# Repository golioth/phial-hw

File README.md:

# Phial

A small (~22 mm diameter, round) battery-powered Bluetooth LE sensor board from
Golioth. Rev B.

> **Status:** pre-release cleanup for open-hardware (OSHW) publication.
> Items marked **[UNKNOWN]** below need confirmation before this README is
> final. Everything else was verified against the design files in this repo.

## Hardware summary (Rev B)

| Subsystem | Part / details | Notes |
|-----------|----------------|-------|
| Main SoC  | Nordic nRF54L15-QFAA | Rev B moved from nRF52 BGA to nRF54L15 DFN |
| PMIC      | Nordic nPM2100 (NPM2100-CAAA-R) | coin-cell optimized |
| IMU       | ST LIS2DH12 | 3-axis accelerometer, I2C |
| Microphone| ST MP34DT05TR-A | PDM MEMS mic |
| Audio out | Raltron RDTE-4.000-3030-NS1 | electromagnetic transducer (buzzer) |
| BLE antenna | Taoglas WLA.04 | 2.4 GHz chip antenna |
| NFC       | Taoglas FXC.24.A flex antenna | nets NFC1/NFC2 |
| Display/UI| 16x 0201 LED ring (Kingbright APG0201SEC-TT) | |
| Buttons   | Panasonic EVP-AWED4A + C&K KMS221G | [UNKNOWN] confirm both populated on Rev B |
| Battery   | CR2032 coin cell (HF1N holder) | [UNKNOWN] role of 112TR contact / alternate battery options |
| Debug     | SWD via Tag-Connect | alignment pins on paste layer |

**[UNKNOWN]** The schematic also references an nRF52840-CKAA-F-R (WLCSP) symbol
and a BME280. It is unclear whether these are an alternate/deprecated variant,
DNP on Rev B, or planned future population. Needs a pass against the Rev B BOM.

## Design files

- KiCad 9 project. **Note:** project files are currently named
  `pilulith.*` (the project's former codename). They are being renamed to
  `phial.*` as part of the release cleanup — see the cleanup checklist.
- 6-layer board, 0.8464 mm thick, ENIG finish, JLC06081H (2116/7628) stackup.
- `input/` — local symbol/footprint/3D sources and reference art.
- `pilulith.pretty/` (to be renamed) — project footprints, including Golioth
  and Orleon logo art footprints.

## Manufacturing outputs

**[UNKNOWN / TODO]** Gerbers, drill files, pick-and-place and BOM exports are
not yet committed or attached to a release. The BOM currently lives in
schematic symbol properties (last touched in commit `e64fb58`). A fabrication
package will be attached to a GitHub Release before publication.

## Firmware

Firmware lives in a separate repo: [golioth/phial-fw](https://github.com/golioth/phial-fw)
(currently private).

## License

Hardware in this repository is released under the **CERN Open Hardware
Licence v2 — Permissive (CERN-OHL-P)**. The LICENSE file is being added as
part of the release cleanup. Documentation and artwork are covered by the
same license unless noted otherwise.

Note: `input/art/` contains vendor reference images (Nordic, JLCPCB stackups,
Taoglas antenna drawings) that are **not** covered by this license and may be
replaced with links before publication — see the cleanup checklist.

## Credits

Designed by Chris Gammell at Golioth.

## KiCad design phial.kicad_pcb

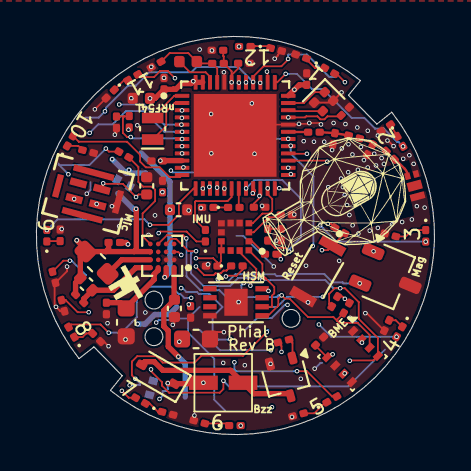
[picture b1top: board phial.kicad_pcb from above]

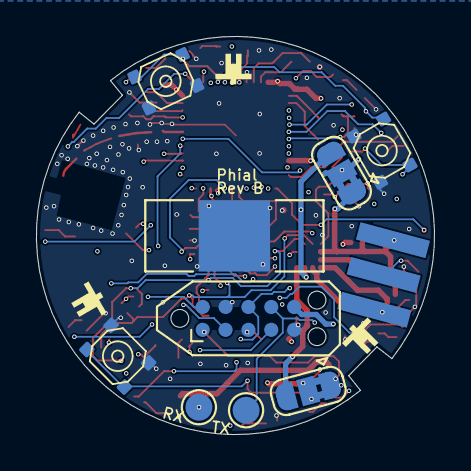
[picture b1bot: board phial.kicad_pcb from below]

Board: 6 copper layers, 22.1 x 22.1 mm, 95 parts (10 on the bottom side), 75 nets.

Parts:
BT101: 112TR; BAT_112TR
C1, C2: 560P; C_0201_0603Metric
C3, C7: 2U2; C_0201_0603Metric
C4: 10N; C_0201_0603Metric
C5: 2N2; C_0201_0603Metric
C6, C9, C101, C105, C107, C118: 0.1U; C_0201_0603Metric
C8, C117: 1P2; C_0201_0603Metric
C10: 22U; C_0603_1608Metric
C11, C16: 1N; C_0201_0603Metric
C12, C108: 10U; C_0402_1005Metric
C13, C14: 2U2; C_0402_1005Metric
C29: 4U7; C_0603_1608Metric
C104: 1U; C_0402_1005Metric
D3: 1N4148W; D_SOD-323
D101, D102, D103, D104, D105, D106, D107, D108, D109, D110, D111, D112: RED; LED_0201_0603Metric
J101: Conn_01x03_Pin; Cabling
J103: Conn_ARM_JTAG_SWD_10; Tag-Connect_TC2050-IDC-NL_2x05_P1.27mm_Vertical
JP1: npm2100-bridge; SolderJumper-3_P1.3mm_Bridged2Bar12_RoundedPad1.0x1.5mm
JP2: sensor-bridge; SolderJumper-3_P1.3mm_Bridged2Bar12_RoundedPad1.0x1.5mm
L1: FB; L_0201_0603Metric
L2: 2u2; L_0603_1608Metric_Pad1.05x0.95mm_HandSolder
L3: 4U7; L_0402_1005Metric
L4: 2N0; L_0201_0603Metric
L101: 3N9; L_0201_0603Metric
L102: 4N7; L_0201_0603Metric
LED13, LED14, LED15, LED16: RED; LED_0201_0603Metric
LS1: RDTE-4.000-3030-NS1
Q1: SBC847; SOT-323_SC-70
R1, R2, R3, R5, R101, R102, R103, R104, R105, R106, R107, R108, R109, R110, R111, R112: R_Small; R_0201_0603Metric
R4, R6, R8, R66: 0; R_0201_0603Metric
R7: 1K; R_0201_0603Metric
R113, R114, R115: 100K; R_0201_0603Metric
R117, R118: 4K7; R_0201_0603Metric
SW1, SW2, SW3: KMT221NG
SW4: KMT221NG; SW_EVP-AWED4A
TP14, TP15: TestPoint; TestPoint_Pad_D1.5mm
U1: NRF54L15-QFAA-R; QFN40P600X600X90-49N
U2: NPM2100-CAAA-R; BGA16N44P4X4_189X191X52N
U10: LIS2DH; SENSOR_LIS2DH12
U102: WLA.04; SMD4_ANT_WLAp04_TAL
U103: ATECC608B-MAHDA; DFN-8-1EP_3x2mm_P0.5mm_EP1.3x1.5mm
U104: LF21115TMR; TSOT-23
U105: BME280; Bosch_LGA-8_2.5x2.5mm_P0.65mm_ClockwisePinNumbering
U106: MP34DT05TR-A; MP34DT05TR-A_STM
Y101: 32MHz; Crystal_SMD_1210-4Pin_1.2x1.0mm
Y102: 32.768K; Crystal_SMD_MicroCrystal_CM9V-T1A-2Pin_1.6x1.0mm

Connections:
/2.07/T0: LED16.2 (A), U1.18 (P2.07/TRACEDATA(0)/SWO)
/2.08/T1: LED13.2 (A), U1.19 (P2.08/TRACEDATA(1))
/2.09/T2: LED14.2 (A), U1.20 (P2.09/TRACEDATA(2))
/2.10/T3: LED15.2 (A), U1.21 (P2.10/TRACEDATA(3))
/ANT_FEED: L4.2, U102.1 (RF_FEED)
/ANT_NRF: L101.1, U1.31 (ANT)
/ANT_PI: C117.2, L101.2, L102.1
/BATTERY_MEAS: R113.1, R114.2, U1.7 (P1.06/ASO(1)/AIN2)
/BOOT: R8.1, SW1.1, SW2.1, SW3.1, U1.40 (P1.12/ASI(3)/RADIO(3)/AIN5)
/BUZZER: R7.1, U1.29 (P0.04/GRTCLFCLKOUT)
/CR2032_V+: C11.1, C12.1, J101.3, JP1.1 (A), L2.1, R6.1, U2.C4 (VBAT)
/IMU_INT: U1.39 (P1.11/ASO(3)/RADIO(2)/AIN4), U10.12 (INT1)
/LED01: D101.2 (A), U1.38 (P1.10/ASI(2)/RADIO(1))
/LED02: D102.2 (A), U1.37 (P1.09/ASO(2)/RADIO(0))
/LED03: D103.2 (A), U1.28 (P0.03/GRTCPWM)
/LED04: D104.2 (A), U1.27 (P0.02)
/LED05: D105.2 (A), U1.17 (P2.06/TRACECLK)
/LED06: D106.2 (A), U1.16 (P2.05)
/LED07: D107.2 (A), U1.15 (P2.04)
/LED08: D108.2 (A), U1.14 (P2.03)
/LED09: D109.2 (A), U1.13 (P2.02)
/LED10: D110.2 (A), U1.12 (P2.01)
/LED11: D111.2 (A), U1.11 (P2.00)
/LED12: D112.2 (A), U1.42 (P1.14/RADIO(5)/AIN7)
/MAG: U1.41 (P1.13/RADIO(4)/AIN6), U104.2 (OUT)
/MIC_CLK: U1.6 (P1.05/ASI(0)/RADIO(6)/AIN1), U106.3 (CLK)
/MIC_DATA: U1.5 (P1.04/ASO(0)/AIN0), U106.4 (DOUT)
/NFC1: C1.1, J101.1, U1.3 (P1.02/NFC1)
/NFC2: C2.2, J101.2, U1.4 (P1.03/NFC2)
/Power_Insert: J103.6 (SWO/TDO), R6.2
/RESET_N: R66.1, SW4.1, U1.30 (~RESET), U2.C1 (PG/RESET)
/SCL: R117.2, U1.24 (P0.01), U2.D2 (SCL), U10.1 (SCL/SPC), U103.6 (SCL), U105.4 (SCK)
/SDA: R118.2, U1.23 (P0.00), U2.D3 (SDA), U10.4 (SDA/SDI/SDO), U103.5 (SDA), U105.3 (SDI)
/SW: L2.2, U2.B4 (SW)
/SWCLK: J103.4 (SWCLK/TCK), U1.26 (SWDCLK)
/SWDIO: J103.2 (SWDIO/TMS), U1.25 (SWDIO)
/VINT-NPM2100: C10.1, C16.1, U2.A3 (VINT)
/VOUT-NPM2100: C14.1, JP1.3 (B), U2.A2 (VOUT)
/VOUTLDO-NPM2100: C13.1, JP2.3 (B), U2.A1 (LSOUT/VOUTLDO)
/nRF52_RX: J103.8 (NC/TDI/RX), TP15.1, U1.8 (P1.07/ASI(1)/AIN3)
/nRF52_TX: J103.7 (TX), TP14.1, U1.9 (P1.08/CLK16M/EXTREF)
DCC: L3.2, U1.46 (DCC)
DECA: C3.1, C4.1, C5.1, L1.1, U1.33 (DECRF), U1.43 (DECA)
DECD: C7.1, L1.2, L3.1, U1.45 (DECD)
GND: BT101.N, C1.2, C2.1, C3.2, C4.2, C5.2, C6.2, C7.2, C8.1, C9.2, C10.2, C13.2, C14.2, C16.2, C29.2, C101.2, C104.2, C105.2, C107.2, C108.2, C117.1, C118.2, J103.3 (GND), J103.5 (GND), J103.9 (GNDDetect), Q1.2 (E), R1.2, R2.2, R3.2, R4.1, R5.2, R101.2, R102.2, R103.2, R104.2, R105.2, R106.2, R107.2, R108.2, R109.2, R110.2, R111.2, R112.2, R114.1, SW1.2, SW2.2, SW3.2, SW4.2, U1.32 (VSS_PA), U1.44 (VSS), U1.49 (VSS), U2.B1 (AVSS1), U2.B2 (AVSS2), U10.5 (RES_5), U10.6 (GND), U10.7 (GND), U10.8 (GND), U102.3 (GND), U102.4 (GND), U103.4 (GND), U103.9 (EP), U104.3 (GND), U105.1 (GND), U105.5 (SDO), U105.7 (GND), U106.5 (GND), Y101.2, Y101.4
unnamed: C8.2, L4.1, L102.2
unnamed: D3.2 (A), LS1.2, Q1.3 (C)
unnamed: D101.1 (K), R101.1
unnamed: D102.1 (K), R102.1
unnamed: D103.1 (K), R103.1
unnamed: D104.1 (K), R104.1
unnamed: D105.1 (K), R105.1
unnamed: D106.1 (K), R106.1
unnamed: D107.1 (K), R107.1
unnamed: D108.1 (K), R108.1
unnamed: D109.1 (K), R109.1
unnamed: D110.1 (K), R110.1
unnamed: D111.1 (K), R111.1
unnamed: D112.1 (K), R112.1
unnamed: J103.10 (~RESET), R66.2
unnamed: LED13.1 (K), R1.1
unnamed: LED14.1 (K), R5.1
unnamed: LED15.1 (K), R2.1
unnamed: LED16.1 (K), R3.1
unnamed: Q1.1 (B), R7.2
unnamed: U1.1 (P1.00/XL1), Y102.2
unnamed: U1.2 (P1.01/XL2), Y102.1
unnamed: U1.34 (XC1), Y101.3
unnamed: U1.35 (XC2), Y101.1
unnamed: C11.2, C12.2, U2.A4 (PVSS)
unnamed: R8.2, U2.D4 (SHPHLD)
unnamed: R115.1, U10.2 (CS)
unnamed: R4.2, U10.3 (SDO/SA0)
VCC: C6.1, C9.1, C101.1, C107.1, C108.1, J103.1 (VTref), JP1.2 (C), JP2.1 (A), R113.2, U1.10 (VDD), U1.22 (VDD), U1.36 (VDD), U1.47 (VDD), U1.48 (VDD)
VSENSOR: C29.1, C104.1, C105.1, C118.1, D3.1 (K), JP2.2 (C), LS1.1, R115.2, R117.1, R118.1, U10.9 (VDD), U10.10 (VDD_IO), U103.8 (VCC), U104.1 (VCC), U105.2 (CSB), U105.6 (VDDIO), U105.8 (VDD), U106.1 (VDD)

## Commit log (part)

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2025-03-07 DRC passes
2025-03-07 Removing additional warnings
2025-03-07 added logo and changed for cheaper process. Found out it's a 22 mm board, whoops
2025-03-07 Rotated battery connector to match the spirulo board cabling
2026-01-15 Modified to use nRF54L15 and DFN instead of BGA nRF52. Moving parts to match
2026-01-16 initial routing complete
2026-01-16 reenable stackup graphic
2026-01-19 putting in a no popped npm2100 for future proofing
2026-01-20 rev b first pass done with no violatio ns
2026-01-20 added second notch and moved associated components
2026-01-23 add updated spirulo design into 3d space
2026-01-23 fix missing connections on npm2100
2026-01-23 add tag connect alignment pins to paste layer
2026-02-19 add part info to BOM
